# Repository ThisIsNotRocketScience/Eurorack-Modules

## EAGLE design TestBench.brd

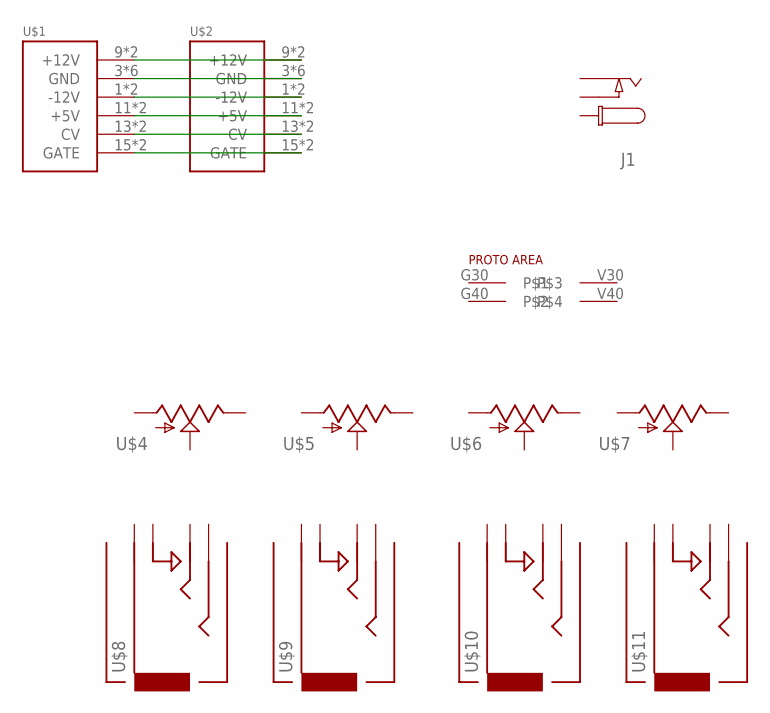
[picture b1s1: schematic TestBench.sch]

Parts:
J1: CON_DC_M-DC_PTH; DC_BARREL_JACK_PTH_2MM
U$1, U$2: POWER; POWER_16
U$3: PROTOAREA; PROTO_10_24
U$4, U$5, U$6, U$7: POTZEPHPOT; OG-POTS_ALPS_POT_VERTICAL
U$8, U$9, U$10, U$11: AUDIO-JACKOUTPUT; 3.5MM-JACK-SWITCH-13MM-OUTPUT

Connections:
unnamed: U$1.9 (+12V), U$1.10 (+12V), U$2.9 (+12V), U$2.10 (+12V)
unnamed: U$1.3 (GND), U$1.4 (GND), U$1.5 (GND), U$1.6 (GND), U$1.7 (GND), U$1.8 (GND), U$2.3 (GND), U$2.4 (GND), U$2.5 (GND), U$2.6 (GND), U$2.7 (GND), U$2.8 (GND)
unnamed: U$1.1 (-12V), U$1.2 (-12V), U$2.1 (-12V), U$2.2 (-12V)
unnamed: U$1.11 (+5V), U$1.12 (+5V), U$2.11 (+5V), U$2.12 (+5V)
unnamed: U$1.13 (CV), U$1.14 (CV), U$2.13 (CV), U$2.14 (CV)
unnamed: U$1.15 (GATE), U$1.16 (GATE), U$2.15 (GATE), U$2.16 (GATE)

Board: 2 copper layers, 12 parts (1 on the bottom side), 6 nets, no tracks yet.

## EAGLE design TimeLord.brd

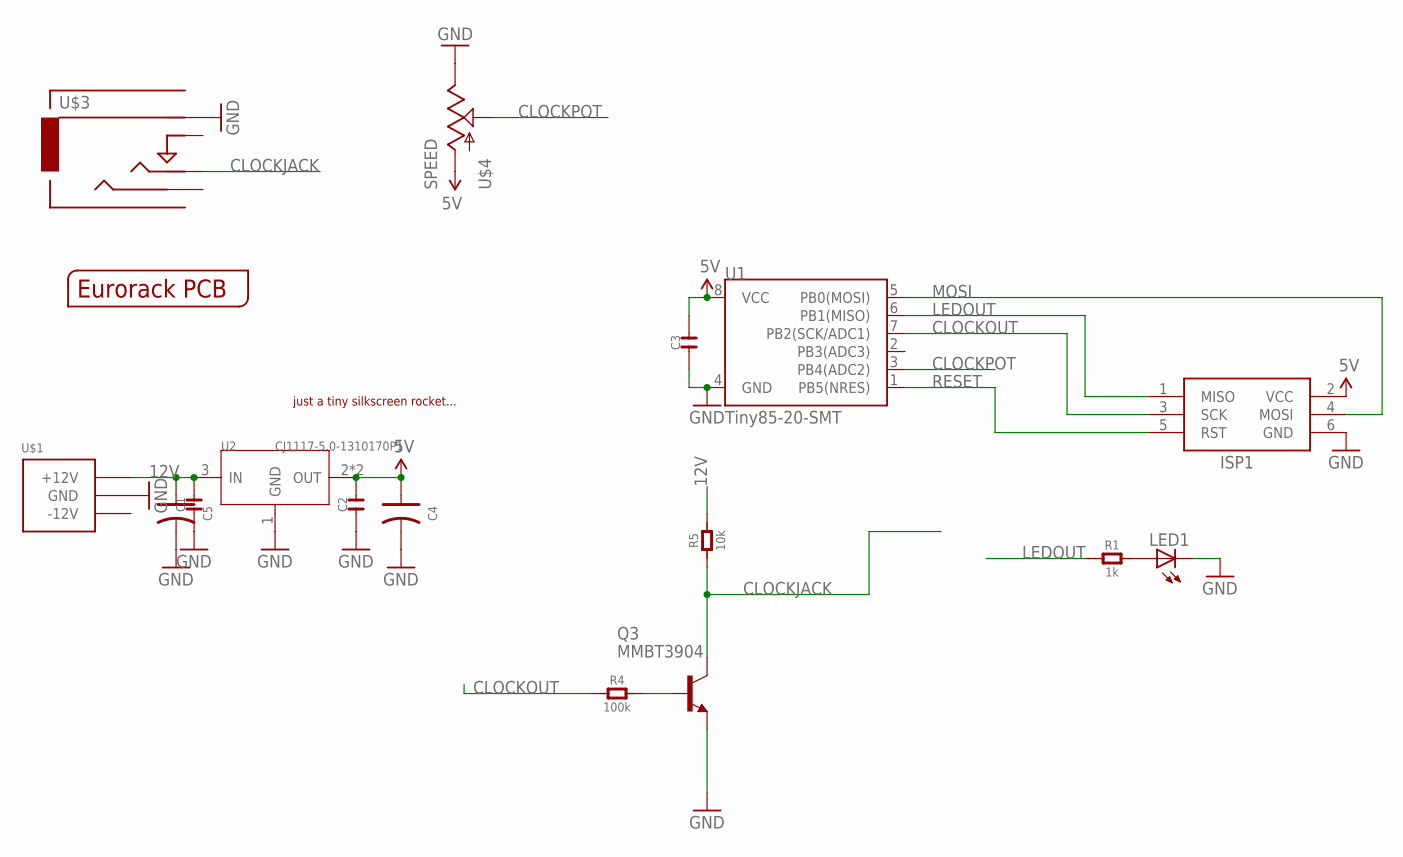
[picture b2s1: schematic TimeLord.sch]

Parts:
C1, C2, C3: C-0603; C0603
C4, C5: C-POLAR-A; AVX-A
ISP1: AVRISP-6; AVRISP
LED1: LED3MM
Q3: MMBT3904; SOT23-BEC
R1: 1k; R0603
R4: 100k; R0603
R5: 10k; R0603
U1: Tiny85-20-SMT; SO08-EIAJ
U2: CJ1117-5.0-1310170P1; SOT223
U$1: POWER_SIMPLE10; POWER_10
U$2: EURORACK_PCB4HP; EURORACK4HPPCB
U$3: CLOCK; 3.5MM-JACK-SWITCH-13MM-OUTPUT
U$4: SPEED; OG-POTS_ALPS_POT_VERTICAL
U$5: JUSTATINYROCKET

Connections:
5V: C2.2, C3.2, C4.+ (1), ISP1.2 (VCC), U1.8 (VCC), U2.2 (OUT), U2.TER (OUT), U$4.P$3 (A)
12V: C1.2, C5.+ (1), R5.2, U2.3 (IN), U$1.9 (+12V), U$1.10 (+12V)
CLOCKJACK: Q3.C, R5.1, U$3.TIP@1 (TIP), U$3.TIP@2 (TIP)
CLOCKOUT: ISP1.3 (SCK), R4.1, U1.7 (PB2(SCK/ADC1))
CLOCKPOT: U1.3 (PB4(ADC2)), U$4.P$2 (S)
GND: C1.1, C2.1, C3.1, C4.- (2), C5.- (2), ISP1.6 (GND), LED1.K (C), Q3.E, U1.4 (GND), U2.1 (GND), U$1.3 (GND), U$1.4 (GND), U$1.5 (GND), U$1.6 (GND), U$1.7 (GND), U$1.8 (GND), U$3.RING@1 (RING), U$3.RING@2 (RING), U$4.P$1 (E)
LEDOUT: ISP1.1 (MISO), R1.1, U1.6 (PB1(MISO))
MOSI: ISP1.4 (MOSI), U1.5 (PB0(MOSI))
unnamed: LED1.A, R1.2
unnamed: Q3.B, R4.2
RESET: ISP1.5 (RST), U1.1 (PB5(NRES))

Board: 2 copper layers, 18 parts (0 on the bottom side), 11 nets, no tracks yet.

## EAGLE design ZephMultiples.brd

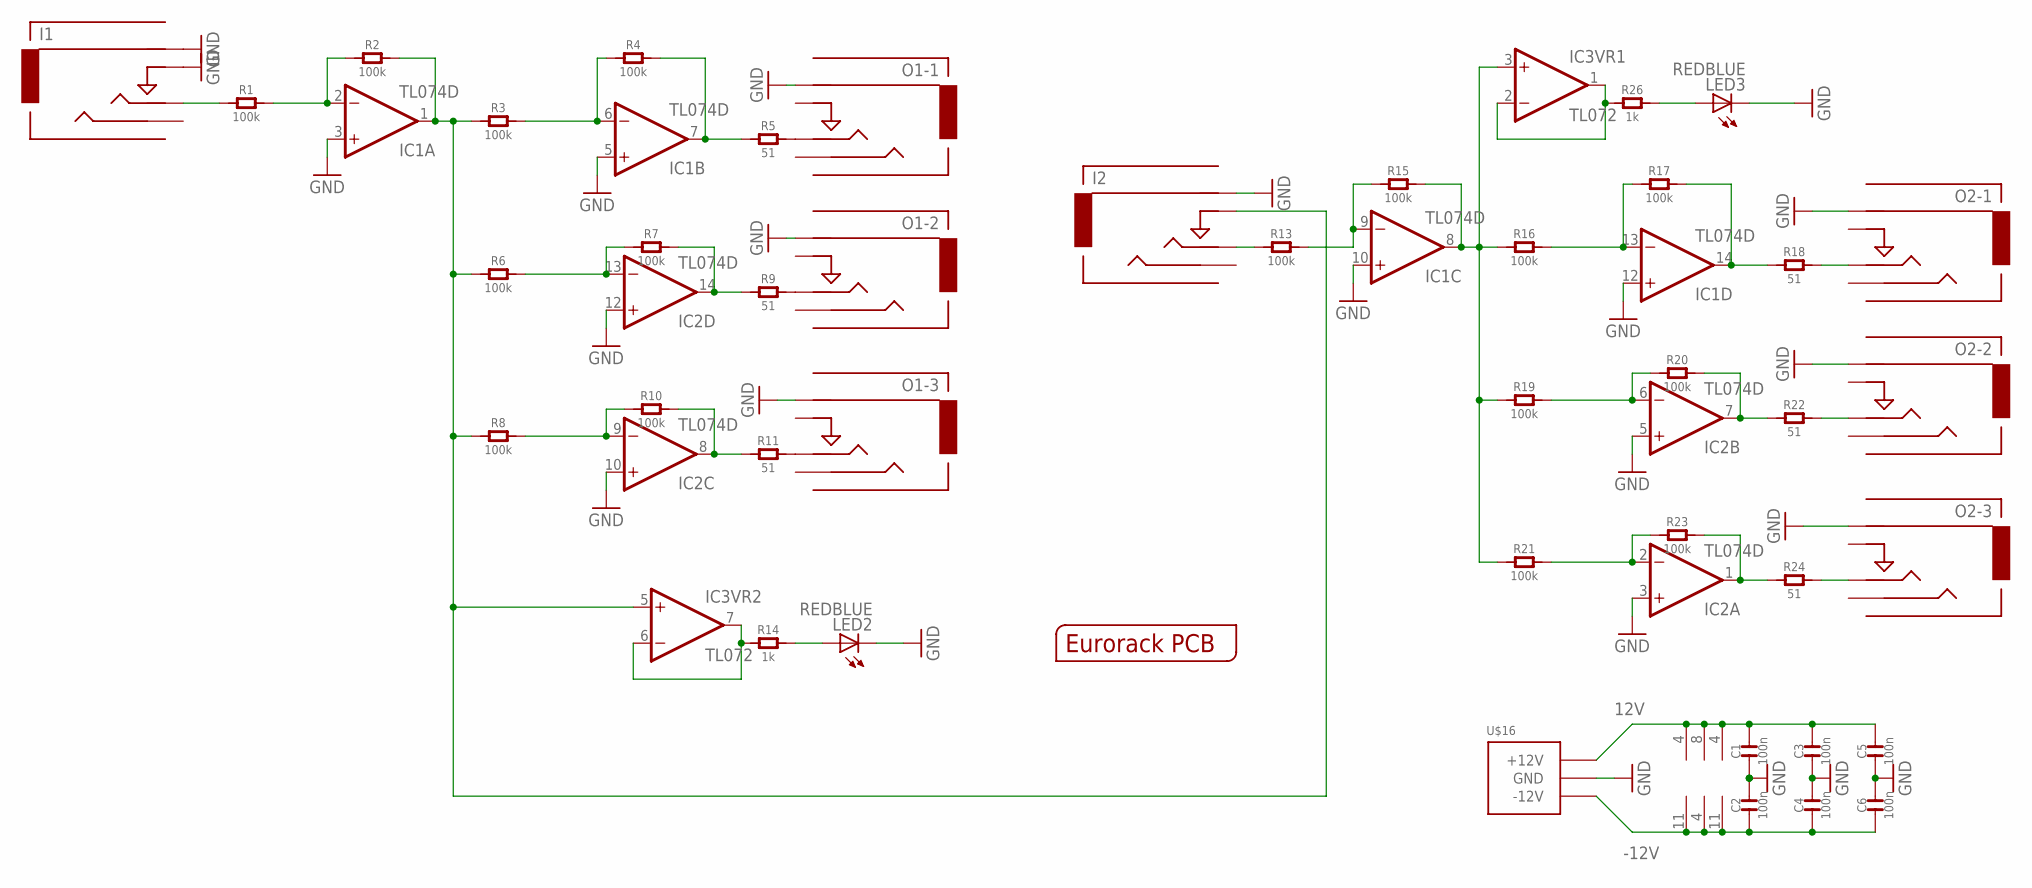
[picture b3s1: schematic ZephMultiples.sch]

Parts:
C1, C2, C3, C4, C5, C6: 100n; C0603
I1: In 1; 3.5MM-JACK-SWITCH-13MM-INPUT
I2: In 2; 3.5MM-JACK-SWITCH-13MM-INPUT
IC1, IC2: TL074D; SO14
IC3: TL072; SO08
LED2, LED3: REDBLUE; LED3MM
O1-1, O1-2, O1-3, O2-1, O2-2, O2-3: AUDIO-JACKOUTPUT; 3.5MM-JACK-SWITCH-13MM-OUTPUT
R1, R2, R3, R4, R6, R7, R8, R10, R13, R15, R16, R17, R19, R20, R21, R23: 100k; R0603
R5, R9, R11, R18, R22, R24: 51; R0603
R14, R26: 1k; R0603
U$15: EURORACK_PCB4HP; EURORACK4HPPCB
U$16: POWER_SIMPLE10-OTHERSIDE; POWER_10_LABELSOTHERSIDE

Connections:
12V: C1.2, C3.2, C5.2, IC1.4 (V+), IC2.4 (V+), IC3.8 (V+), U$16.9 (+12V), U$16.10 (+12V)
-12V: C2.1, C4.1, C6.1, IC1.11 (V-), IC2.11 (V-), IC3.4 (V-), U$16.1 (-12V), U$16.2 (-12V)
GND: C1.1, C2.2, C3.1, C4.2, C5.1, C6.2, I1.RING@1 (RING), I1.RING@2 (RING), I1.SWITCH@1 (SWITCH), I1.SWITCH@2 (SWITCH), I2.RING@1 (RING), I2.RING@2 (RING), IC1.3 (+IN), IC1.5 (+IN), IC1.10 (+IN), IC1.12 (+IN), IC2.3 (+IN), IC2.5 (+IN), IC2.10 (+IN), IC2.12 (+IN), LED2.K (C), LED3.K (C), O1-1.RING@1 (RING), O1-1.RING@2 (RING), O1-2.RING@1 (RING), O1-2.RING@2 (RING), O1-3.RING@1 (RING), O1-3.RING@2 (RING), O2-1.RING@1 (RING), O2-1.RING@2 (RING), O2-2.RING@1 (RING), O2-2.RING@2 (RING), O2-3.RING@1 (RING), O2-3.RING@2 (RING), U$16.3 (GND), U$16.4 (GND), U$16.5 (GND), U$16.6 (GND), U$16.7 (GND), U$16.8 (GND)
unnamed: I1.TIP@1 (TIP), I1.TIP@2 (TIP), R1.1
unnamed: IC1.2 (-IN), R1.2, R2.1
unnamed: I2.SWITCH@1 (SWITCH), I2.SWITCH@2 (SWITCH), IC1.1 (OUT), IC3.5 (+IN), R2.2, R3.1, R6.1, R8.1
unnamed: IC1.6 (-IN), R3.2, R4.1
unnamed: IC1.7 (OUT), R4.2, R5.1
unnamed: IC2.13 (-IN), R6.2, R7.1
unnamed: IC2.9 (-IN), R8.2, R10.1
unnamed: IC2.14 (OUT), R7.2, R9.1
unnamed: IC2.8 (OUT), R10.2, R11.1
unnamed: O1-1.TIP@1 (TIP), O1-1.TIP@2 (TIP), R5.2
unnamed: O1-2.TIP@1 (TIP), O1-2.TIP@2 (TIP), R9.2
unnamed: O1-3.TIP@1 (TIP), O1-3.TIP@2 (TIP), R11.2
unnamed: I2.TIP@1 (TIP), I2.TIP@2 (TIP), R13.1
unnamed: IC1.9 (-IN), R13.2, R15.1
unnamed: IC1.8 (OUT), IC3.3 (+IN), R15.2, R16.1, R19.1, R21.1
unnamed: IC1.13 (-IN), R16.2, R17.1
unnamed: IC1.14 (OUT), R17.2, R18.1
unnamed: IC2.6 (-IN), R19.2, R20.1
unnamed: IC2.2 (-IN), R21.2, R23.1
unnamed: IC2.7 (OUT), R20.2, R22.1
unnamed: IC2.1 (OUT), R23.2, R24.1
unnamed: O2-1.TIP@1 (TIP), O2-1.TIP@2 (TIP), R18.2
unnamed: O2-2.TIP@1 (TIP), O2-2.TIP@2 (TIP), R22.2
unnamed: O2-3.TIP@1 (TIP), O2-3.TIP@2 (TIP), R24.2
unnamed: IC3.6 (-IN), IC3.7 (OUT), R14.1
unnamed: IC3.1 (OUT), IC3.2 (-IN), R26.1
unnamed: LED2.A, R14.2
unnamed: LED3.A, R26.2

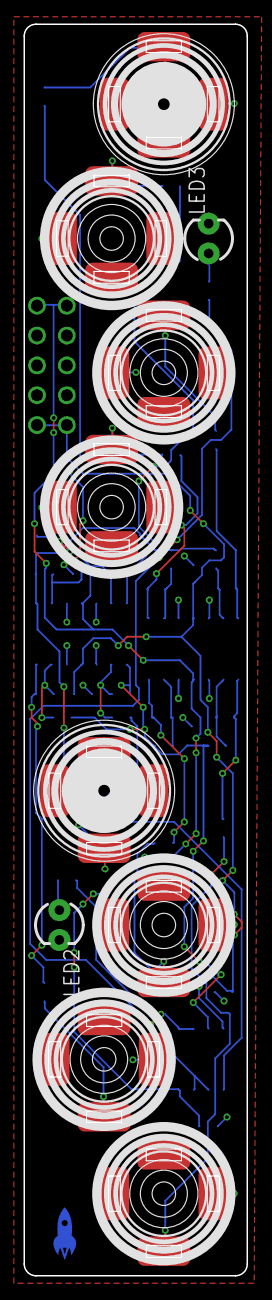
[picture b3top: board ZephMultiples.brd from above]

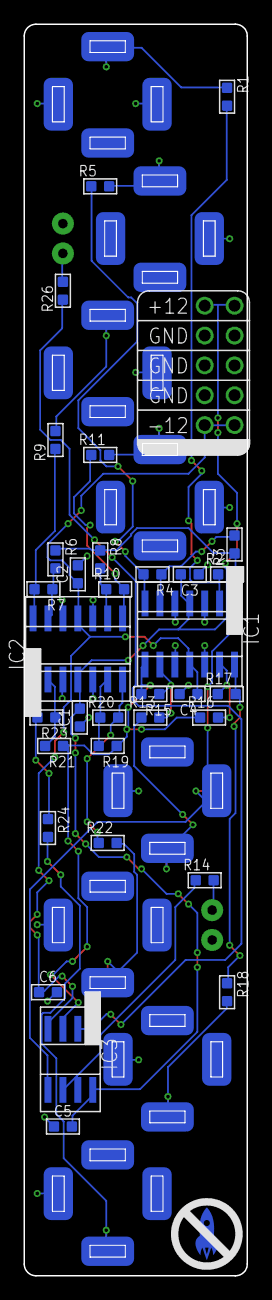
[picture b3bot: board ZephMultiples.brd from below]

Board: 2 copper layers, 19.0 x 106.5 mm, 46 parts (35 on the bottom side), 31 nets.

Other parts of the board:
U$1: SMALLROCKET

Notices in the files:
parts and their libraries:
SparkFun-LED: Licensing: CC v3.0 Share-Alike You are welcome to use this library for commercial purposes.
